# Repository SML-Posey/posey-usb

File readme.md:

# Posey USB Dongle

This dongle breaks out the USB connector to get the SWD lines, I2C, and 5V power. It is assumed a USB cable will be used, wherein a few of the pins are swapped.

## License

Shield: [![CC BY-SA 4.0][cc-by-sa-shield]][cc-by-sa]

This work is licensed under a
[Creative Commons Attribution-ShareAlike 4.0 International License][cc-by-sa].

[![CC BY-SA 4.0][cc-by-sa-image]][cc-by-sa]

[cc-by-sa]: http://creativecommons.org/licenses/by-sa/4.0/
[cc-by-sa-image]: https://licensebuttons.net/l/by-sa/4.0/88x31.png
[cc-by-sa-shield]: https://img.shields.io/badge/License-CC%20BY--SA%204.0-lightgrey.svg

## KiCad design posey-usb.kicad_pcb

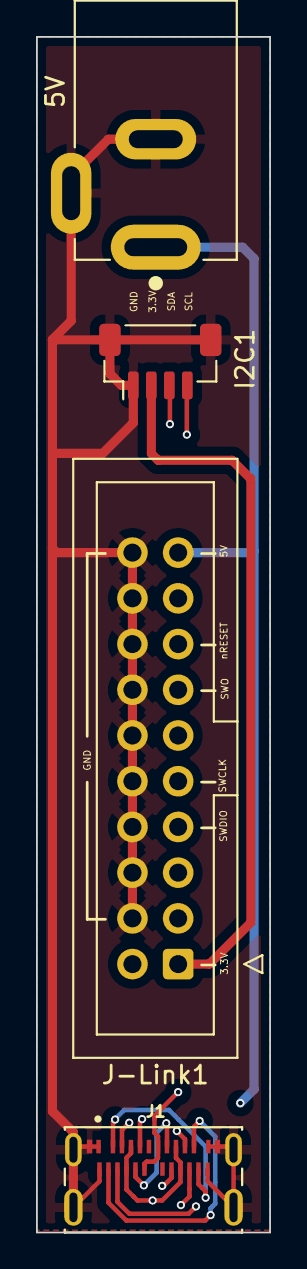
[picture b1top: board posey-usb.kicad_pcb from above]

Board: 4 copper layers, 13.0 x 66.4 mm, 4 parts (0 on the bottom side), 9 nets.

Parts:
5V: PJ-002A; CUI_PJ-002A
I2C1: I2C; JST_SH_BM04B-SRSS-TB_1x04-1MP_P1.00mm_Vertical
J1: USB-C Recp TE-2305018-2; TE_2305018-2_USBC_Recepticle
J-Link1: J-Link; IDC-Header_2x10_P2.54mm_Vertical

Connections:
3.3V: I2C1.2, J1.A5 (CC1), J1.B5 (CC2), J-Link1.1
5V: 5V.1, J1.A4 (VBUS_A), J1.A9 (VBUS_A), J1.B4 (VBUS_B), J1.B9 (VBUS_B), J-Link1.19
GND: 5V.2, 5V.3, I2C1.1, J1.A1 (GNDA), J1.A12 (GNDA), J1.B1 (GNDB), J1.B12 (GNDB), J1.G1 (GND), J1.G2 (GND), J1.S1 (SHIELD), J1.S2 (SHIELD), J1.S3 (SHIELD), J1.S4 (SHIELD), J-Link1.4, J-Link1.6, J-Link1.8, J-Link1.10, J-Link1.12, J-Link1.14, J-Link1.16, J-Link1.18, J-Link1.20
SCL: I2C1.4, J1.A3 (TX1_N), J1.B3 (TX2_N)
SDA: I2C1.3, J1.A2 (TX1_P), J1.B2 (TX2_P)
SWCLK: J1.A11 (RX2_P), J1.B11 (RX1_P), J-Link1.9
SWDIO: J1.A10 (RX2_N), J1.B10 (RX1_N), J-Link1.7
SWO: J1.A7 (DA_N), J1.B7 (DB_N), J-Link1.13
nRESET: J1.A8 (SBU1), J1.B8 (SBU2), J-Link1.15

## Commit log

2022-04-11 Initial
2022-04-24 Updated license.
